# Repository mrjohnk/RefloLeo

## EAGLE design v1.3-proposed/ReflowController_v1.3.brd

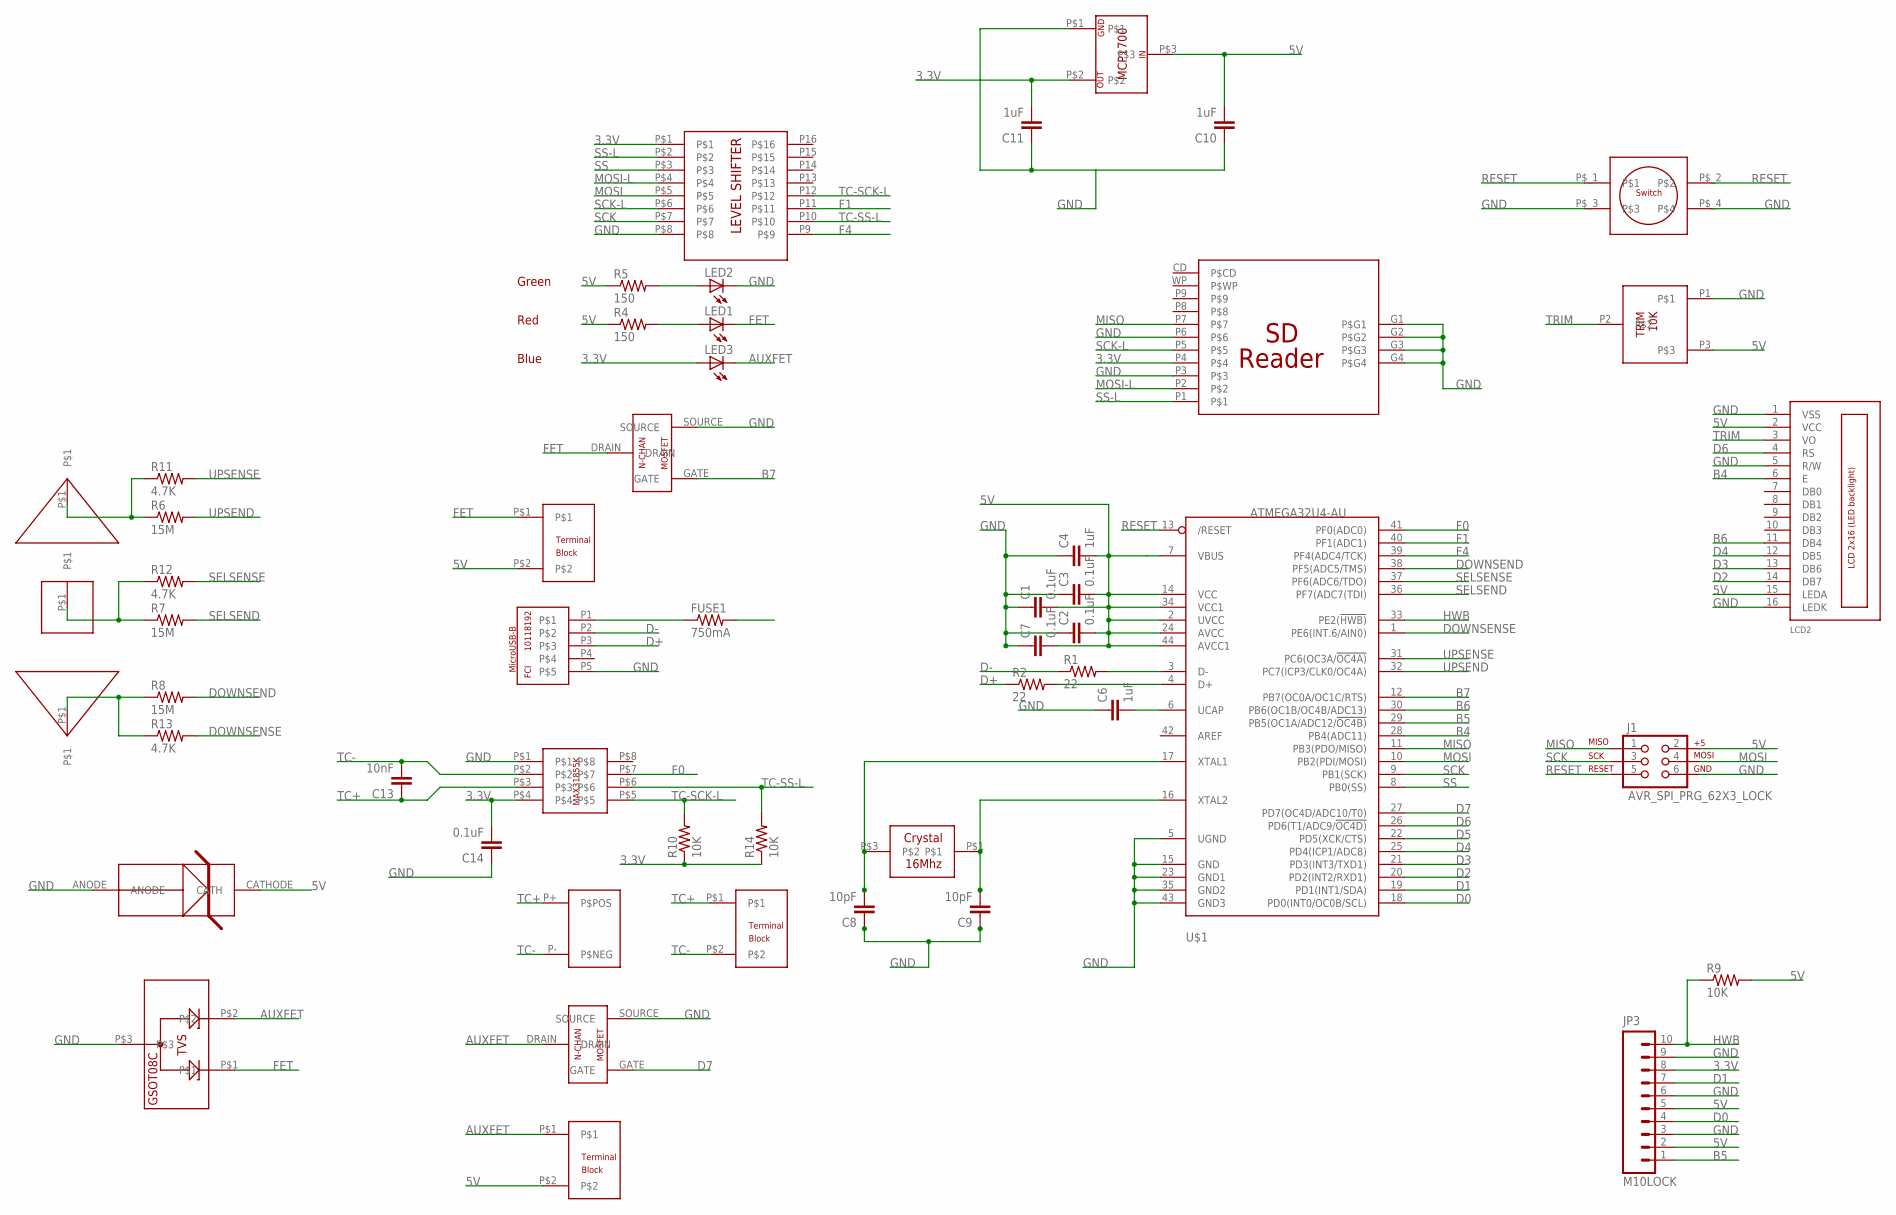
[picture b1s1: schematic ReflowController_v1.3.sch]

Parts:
C1, C2, C3, C7, C14: 0.1uF; 0603-CAP
C4, C6, C10, C11: 1uF; 0603-CAP
C8, C9: 10pF; 0603-CAP
C13: 10nF; 0603-CAP
FUSE1: 750mA; 0603-RES
J1: AVR_SPI_PRG_62X3_LOCK; 2X3_LOCK
JP3: M10LOCK; 1X10_LOCK
LCD2: LCD_2X16_SIL; HY-1602F
LED1, LED2, LED3: LED0603; LED-0603
R1, R2: 22; 0603-RES
R4, R5: 150; 0603-RES
R6, R7, R8: 15M; 0603-RES
R9, R10, R14: 10K; 0603-RES
R11, R12, R13: 4.7K; 0603-RES
U$1: ATMEGA32U4-AU; TQFP44
U$2: 16MHZ-CRYSTAL_NX3225GA-16.000M-STD-CRG-1
U$3: USB-B_10118192-0001LF
U$4: SDREADER_2041021-4
U$5, U$7, U$17: 2POS_TERM_ED2748-ND
U$6, U$16: N-MOSFET630_DMG1012T-7DICT-ND
U$8: NXP_LVL_SHIFT_74HC4050D,653
U$9: MAX_TC_MAX31855KASA+
U$10: 10K_TRIM_3362F-1-103LF
U$11: MCP1700__LDO
U$12: MOM-SWITCH-EG4620CT-ND
U$13, U$14: CAPTOUCH_ARROW
U$15: CAPTOUCH_SQUARE
U$18: TVS_DIODE_MATRIX_GSOT08C-GS08
U$19: TVS_DIODE_1CH_1SMB6.0AT3G
U$20: CUSTOM_K-TYPE

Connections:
5V: C1.2, C2.2, C3.2, C4.2, C7.2, C10.2, FUSE1.2, J1.2, JP3.2, JP3.5, LCD2.2 (VCC), LCD2.15 (LEDA), R4.1, R5.1, R9.2, U$1.2 (UVCC), U$1.7 (VBUS), U$1.14 (VCC), U$1.24 (AVCC), U$1.34 (VCC1), U$1.44 (AVCC1), U$5.P$2, U$10.P3, U$11.P$3, U$17.P$2, U$19.CATHODE (CATH); also elsewhere on the board
AUXFET: LED3.C, U$16.DRAIN, U$17.P$1, U$18.P$2
B4: LCD2.6 (E), U$1.28 (PB4(ADC11))
B5: JP3.1, U$1.29 (PB5(OC1A/ADC12/!OC4B))
B6: LCD2.11 (DB4), U$1.30 (PB6(OC1B/OC4B/ADC13))
B7: U$1.12 (PB7(OC0A/OC1C/RTS)), U$6.GATE
D0: JP3.4, U$1.18 (PD0(INT0/OC0B/SCL))
D1: JP3.7, U$1.19 (PD1(INT1/SDA))
D2: LCD2.14 (DB7), U$1.20 (PD2(INT2/RXD1))
D3: LCD2.13 (DB6), U$1.21 (PD3(INT3/TXD1))
D4: LCD2.12 (DB5), U$1.25 (PD4(ICP1/ADC8))
D5: U$1.22 (PD5(XCK/CTS))
D6: LCD2.4 (RS), U$1.26 (PD6(T1/ADC9/!OC4D))
D7: U$1.27 (PD7(OC4D/ADC10/T0)), U$16.GATE
D+: R2.1, U$3.P3
D-: R1.1, U$3.P2
DOWNSEND: R8.2, U$1.38 (PF5(ADC5/TMS))
DOWNSENSE: R13.2, U$1.1 (PE6(INT.6/AIN0))
F0: U$1.41 (PF0(ADC0)), U$9.P$7
F1: U$1.40 (PF1(ADC1)), U$8.P11
F4: U$1.39 (PF4(ADC4/TCK)), U$8.P9
FET: LED1.C, U$5.P$1, U$6.DRAIN, U$18.P$1
GND: C1.1, C2.1, C3.1, C4.1, C6.1, C7.1, C8.1, C9.1, C10.1, C11.1, C14.1, J1.6, JP3.3, JP3.6, JP3.9, LCD2.1 (VSS), LCD2.5 (R/W), LCD2.16 (LEDK), LED2.C, U$1.5 (UGND), U$1.15 (GND), U$1.23 (GND1), U$1.35 (GND2), U$1.43 (GND3), U$3.P5, U$4.G1, U$4.G2, U$4.G3, U$4.G4, U$4.P3, U$4.P6, U$6.SOURCE, U$8.P$8, U$9.P$1, U$10.P1, U$11.P$1, U$12.P$_3, U$12.P$_4, U$16.SOURCE, U$18.P$3, U$19.ANODE
HWB: JP3.10, R9.1, U$1.33 (PE2(!HWB))
MISO: J1.1, U$1.11 (PB3(PDO/MISO)), U$4.P7
MOSI: J1.4, U$1.10 (PB2(PDI/MOSI)), U$8.P$5
MOSI-L: U$4.P2, U$8.P$4
unnamed: C8.2, U$1.17 (XTAL1), U$2.P$3
unnamed: C9.2, U$1.16 (XTAL2), U$2.P$1
unnamed: LED1.A, R4.2
unnamed: LED2.A, R5.2
unnamed: FUSE1.1, U$3.P1
unnamed: R1.2, U$1.3 (D-)
unnamed: C6.2, U$1.6 (UCAP)
unnamed: R2.2, U$1.4 (D+)
unnamed: R6.1, R11.1, U$13.P$1
unnamed: R7.1, R12.1, U$15.P$1
unnamed: R8.1, R13.1, U$14.P$1
RESET: J1.5, U$1.13 (/RESET), U$12.P$_1, U$12.P$_2
SCK: J1.3, U$1.9 (PB1(SCK)), U$8.P$7
SCK-L: U$4.P5, U$8.P$6
SELSEND: R7.2, U$1.36 (PF7(ADC7(TDI))
SELSENSE: R12.2, U$1.37 (PF6(ADC6/TDO))
SS: U$1.8 (PB0(SS)), U$8.P$3
SS-L: U$4.P1, U$8.P$2
TC+: C13.1, U$7.P$1, U$9.P$3, U$20.P+ (P$POS)
TC-: C13.2, U$7.P$2, U$9.P$2, U$20.P- (P$NEG)
TC-SCK-L: R10.2, U$8.P12, U$9.P$5
TC-SS-L: R14.2, U$8.P10, U$9.P$6
TRIM: LCD2.3 (VO), U$10.P2
UPSEND: R6.2, U$1.32 (PC7(ICP3/CLK0/OC4A))
UPSENSE: R11.2, U$1.31 (PC6(OC3A/!OC4A))

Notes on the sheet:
Red
Blue
Green

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
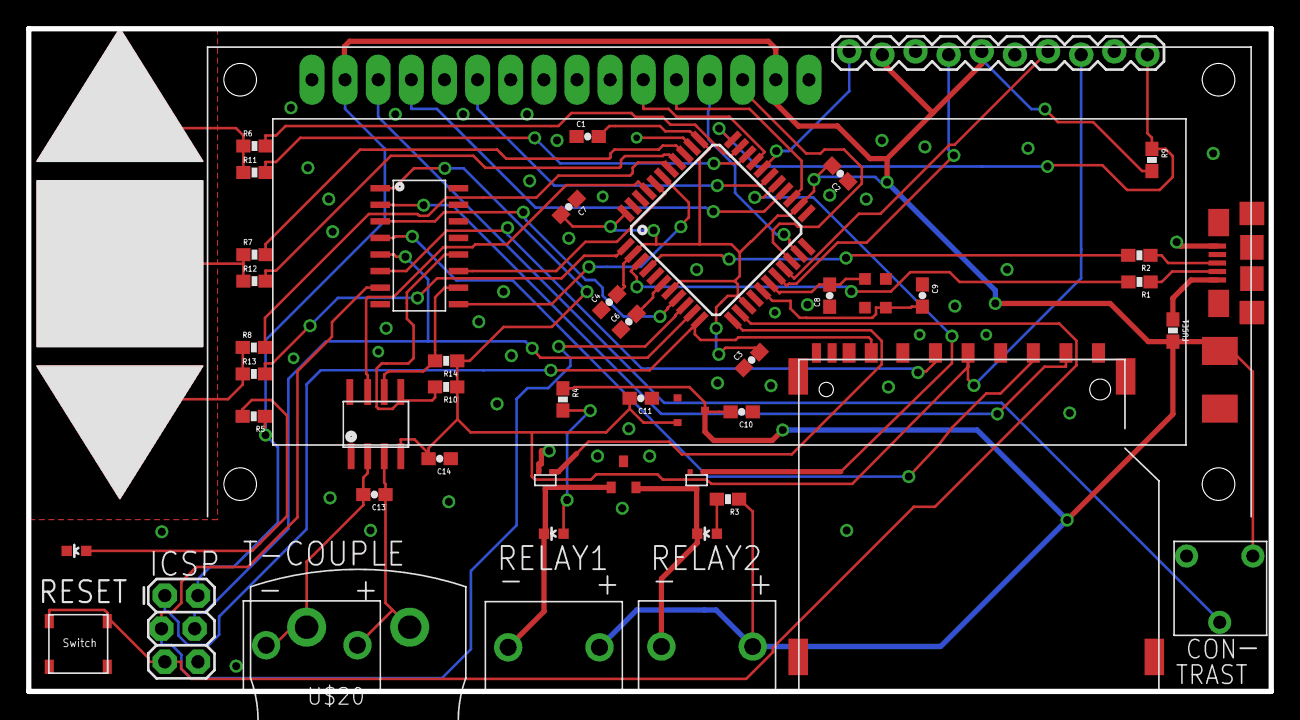
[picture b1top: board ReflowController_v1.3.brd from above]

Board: 2 copper layers, 95.2 x 50.8 mm, 53 parts (0 on the bottom side), 53 nets.

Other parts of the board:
R3: 390; 0603-RES

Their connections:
5V: R3.1; also elsewhere on the board

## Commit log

2013-06-04 RefloLeo
2013-06-08 Version 1.1 prototype
2013-06-16 Oven Profiler
2013-06-18 v1.2 w/Additional Zener Protection Diode
2013-06-23 Arduino sketch for RefloLeo v1.2
2013-06-23 Profile logging added
    Each reflow job will now be logged to a text file on the SD memory card
    to review afterword. Helps develop proper profile and ensure proper
    performance.
2013-07-02 16x2 LCD support and self test added
2013-07-04 16x2 LCD support, self test added, invalid temp
2013-07-07 Added 2 servo interfaces, many pin reassignments
2013-07-10 Added 2 servo interfaces, many pin swaps
2013-07-16 SD Memory Card Files
2013-07-17 Added 2 servo interfaces, many optimizations
2013-07-17 16x2 LCD support, self test added, optimizations
2013-08-08 Relay2=pin3, AnalogWrite Selftest, log bugfix
2013-09-22 Libs used in compiling the RefloLeo firmware
2013-11-17 Minor bug fix for display and memory card files
2014-02-16 User Contributed
2014-02-24 Fixed a bug in the "H" command
2015-03-06 Update and rename v1.2-proposed/UserContributed to v1.2-proposed/UserContributed/refloLeo1_6.ino
    Added Pulse Width Modulation

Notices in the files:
parts and their libraries:
SparkFun-Passives: Licensing: CC v3.0 Share-Alike You are welcome to use this library for commercial purposes.
